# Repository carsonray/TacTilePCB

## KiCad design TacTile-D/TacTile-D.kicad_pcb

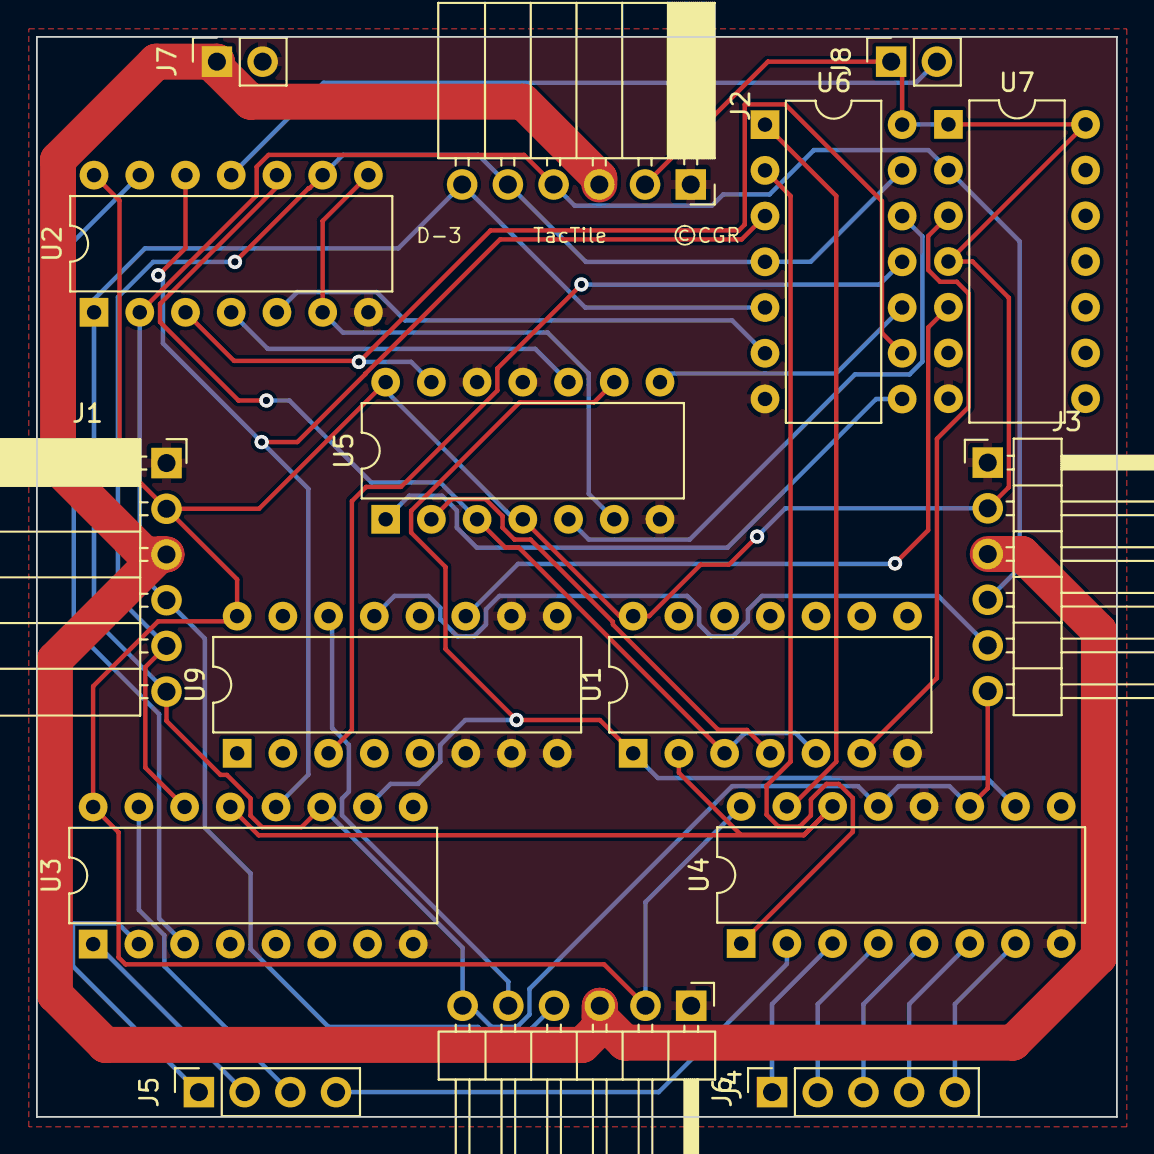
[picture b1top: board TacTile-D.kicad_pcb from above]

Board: 2 copper layers, 60.0 x 60.0 mm, 16 parts (0 on the bottom side), 36 nets.

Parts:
J1, J2: Conn_01x06; PinSocket_1x06_P2.54mm_Horizontal
J3, J4: Conn_01x06; PinHeader_1x06_P2.54mm_Horizontal
J5: Conn_01x04; PinSocket_1x04_P2.54mm_Vertical
J6: Conn_01x05; PinSocket_1x05_P2.54mm_Vertical
J7, J8: Conn_01x02; PinSocket_1x02_P2.54mm_Vertical
U1: 74LS04; DIP-14_W7.62mm
U2: 4011; DIP-14_W7.62mm
U3: 74HC595; DIP-16_W7.62mm
U4: 74HC590; DIP-16_W7.62mm
U5, U7: 74LS74; DIP-14_W7.62mm
U6: 74HC08; DIP-14_W7.62mm
U9: 74HC4051; DIP-16_W7.62mm

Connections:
CLK: J1.6, J2.6, J3.6, J4.6, U2.1, U3.11 (SRCLK), U4.11 (CPC), U4.13 (CPR), U6.5
GND: J1.1, J2.1, J3.1, J4.1, J7.2, U1.7 (GND), U2.7 (VSS), U3.8 (GND), U4.8 (GND), U4.12 (~CE), U5.7 (GND), U5.11 (C), U5.12 (D), U6.7 (GND), U7.7 (GND), U9.6 (~E), U9.7 (VEE), U9.8 (GND), U9.9 (S2), U9.10 (S1)
LEN: J8.2, U2.11
LS0: J5.1, U3.2 (QC)
LS1: J5.2, U3.1 (QB)
LS2: J5.3, U3.15 (QA)
LS3: J5.4, U4.2 (Q2)
LS4: J6.1, U4.3 (Q3)
LS5: J6.2, U4.4 (Q4)
LS6: J6.3, U4.5 (Q5)
LS7: J6.4, U4.6 (Q6)
LS8: J6.5, U4.7 (Q7)
MISO0: J3.5, U9.13 (A0)
MISO1: J4.5, U9.14 (A1)
MOSI: J1.5, J2.5, U2.9, U3.14 (SER), U6.4, U6.13
unnamed: U2.5, U6.6
unnamed: U2.13, U3.3 (QD)
unnamed: U2.12, U3.12 (RCLK), U6.3
unnamed: U1.2, U3.13 (~OE), U4.14 (~OE)
unnamed: U4.15 (Q0), U6.1
unnamed: U4.1 (Q1), U6.2
unnamed: U1.3, U1.5, U2.10, U5.3 (C)
unnamed: U1.4, U5.2 (D)
unnamed: U5.5 (Q), U6.12
unnamed: U2.6, U2.8, U5.6 (~Q)
unnamed: U5.1 (~R), U6.8
unnamed: U5.8 (~Q), U6.10
unnamed: U2.3, U5.13 (~R), U6.9
unnamed: U2.4, U5.10 (~S)
unnamed: U1.6, U7.3 (C)
unnamed: U7.5 (Q), U9.11 (S0)
unnamed: U6.11, U9.3 (A)
SEN: U1.1, U3.10 (~SRCLR), U4.10 (~MRC), U5.9 (Q)
SS: J1.4, J2.4, J3.4, J4.4, U2.2, U7.2 (D)
VCC: J1.2, J2.2, J3.2, J4.2, J8.1, U1.14 (VCC), U2.14 (VDD), U3.16 (VCC), U4.16 (VCC), U5.4 (~S), U5.14 (VCC), U6.14 (VCC), U7.1 (~R), U7.4 (~S), U7.14 (VCC), U9.16 (VCC)
VIN: J1.3, J2.3, J3.3, J4.3, J7.1

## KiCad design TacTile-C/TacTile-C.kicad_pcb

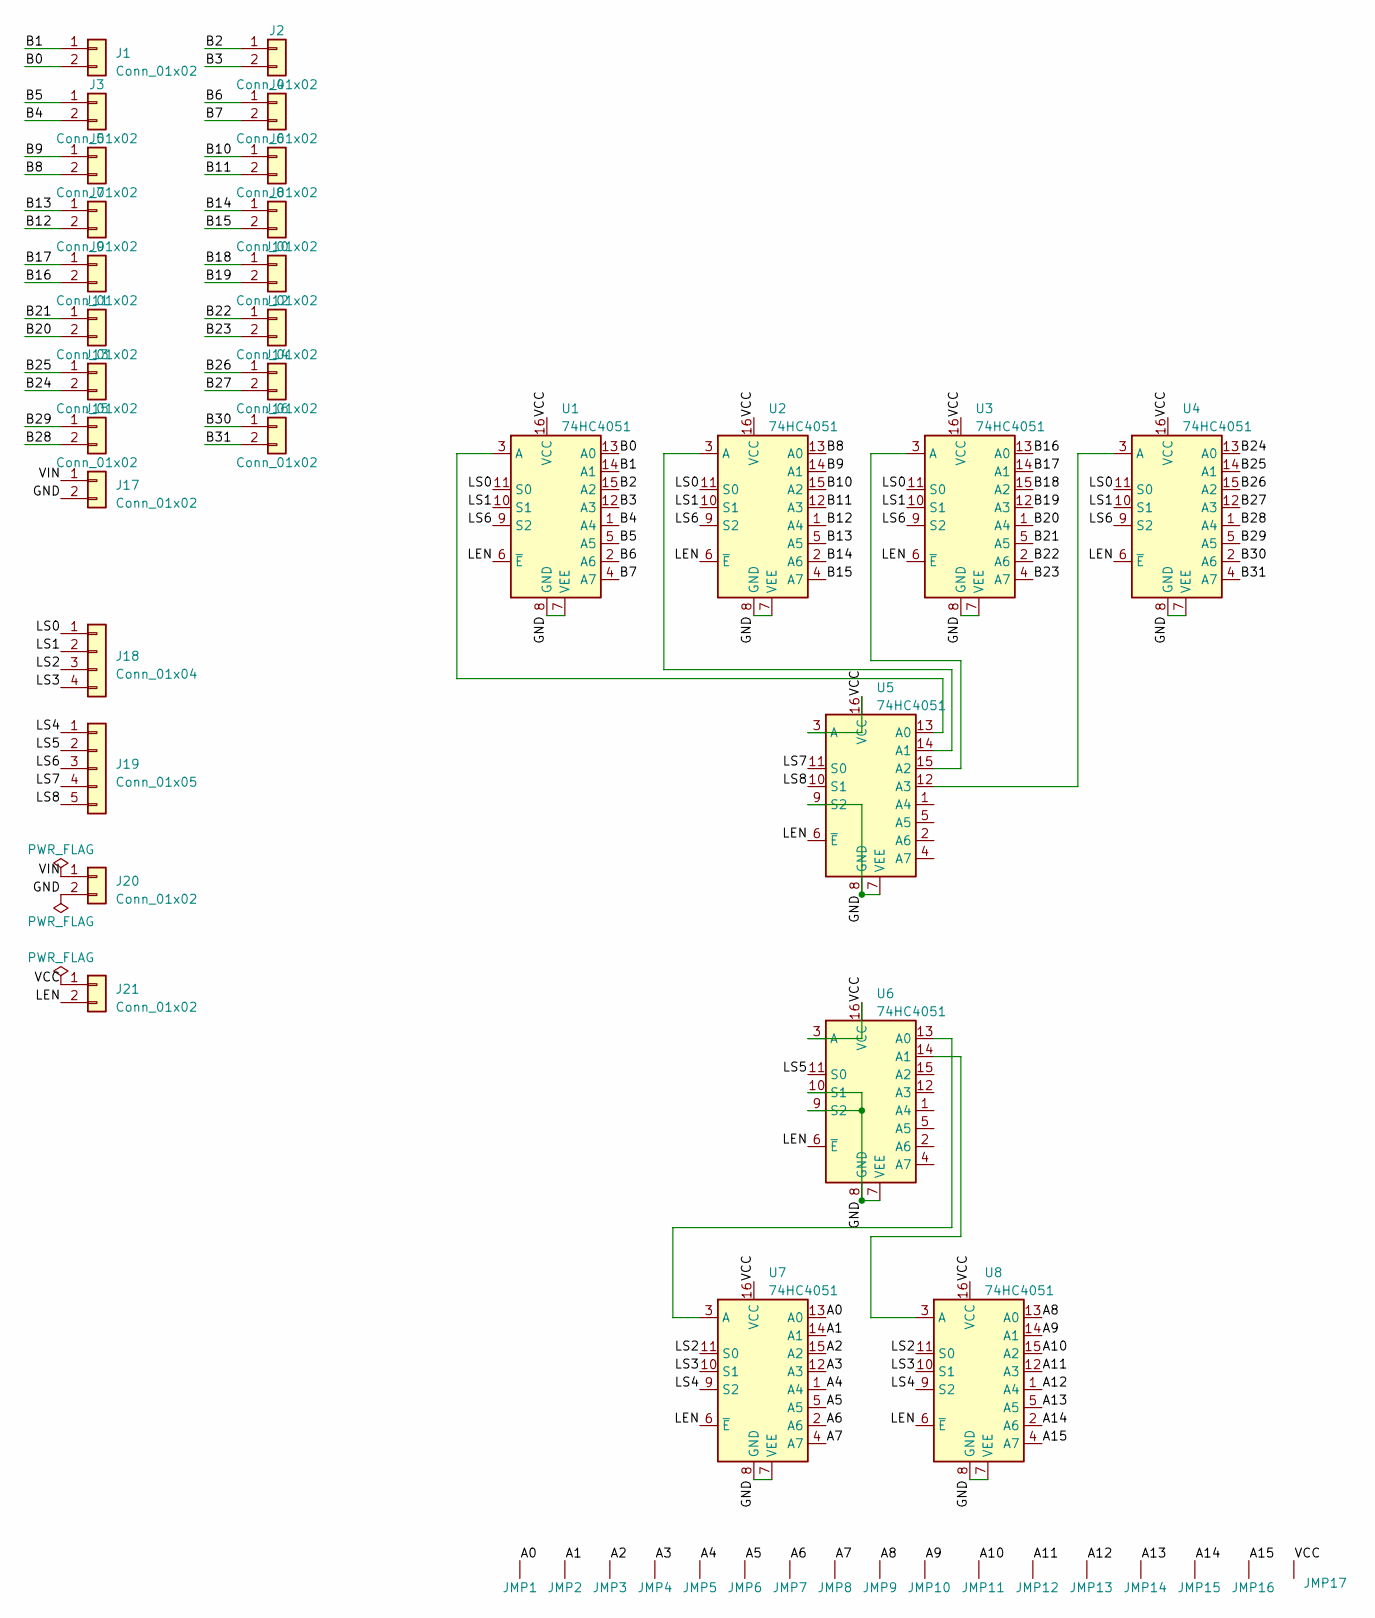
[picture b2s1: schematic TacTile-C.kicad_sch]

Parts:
J1, J2, J3, J4, J5, J6, J7, J8, J9, J10, J11, J12, J13, J14, J15, J16, J17: Conn_01x02; PinSocket_1x02_P1.27mm_Vertical
J18: Conn_01x04; PinHeader_1x04_P2.54mm_Vertical
J19: Conn_01x05; PinHeader_1x05_P2.54mm_Vertical
J20, J21: Conn_01x02; PinHeader_1x02_P2.54mm_Vertical
JMP1, JMP2, JMP3, JMP4, JMP5, JMP6, JMP7, JMP8, JMP9, JMP10, JMP11, JMP12, JMP13, JMP14, JMP15, JMP16, JMP17: Jumper_Connect
U1, U2, U3, U4, U5, U6, U7, U8: 74HC4051; DIP-16_W7.62mm

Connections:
/A0: JMP1.1 (A), U7.13 (A0)
/A1: JMP2.1 (A), U7.14 (A1)
/A2: JMP3.1 (A), U7.15 (A2)
/A3: JMP4.1 (A), U7.12 (A3)
/A4: JMP5.1 (A), U7.1 (A4)
/A5: JMP6.1 (A), U7.5 (A5)
/A6: JMP7.1 (A), U7.2 (A6)
/A7: JMP8.1 (A), U7.4 (A7)
/A8: JMP9.1 (A), U8.13 (A0)
/A9: JMP10.1 (A), U8.14 (A1)
/A10: JMP11.1 (A), U8.15 (A2)
/A11: JMP12.1 (A), U8.12 (A3)
/A12: JMP13.1 (A), U8.1 (A4)
/A13: JMP14.1 (A), U8.5 (A5)
/A14: JMP15.1 (A), U8.2 (A6)
/A15: JMP16.1 (A), U8.4 (A7)
/B0: J1.2, U1.13 (A0)
/B1: J1.1, U1.14 (A1)
/B2: J2.1, U1.15 (A2)
/B3: J2.2, U1.12 (A3)
/B4: J3.2, U1.1 (A4)
/B5: J3.1, U1.5 (A5)
/B6: J4.1, U1.2 (A6)
/B7: J4.2, U1.4 (A7)
/B8: J5.2, U2.13 (A0)
/B9: J5.1, U2.14 (A1)
/B10: J6.1, U2.15 (A2)
/B11: J6.2, U2.12 (A3)
/B12: J7.2, U2.1 (A4)
/B13: J7.1, U2.5 (A5)
/B14: J8.1, U2.2 (A6)
/B15: J8.2, U2.4 (A7)
/B16: J9.2, U3.13 (A0)
/B17: J9.1, U3.14 (A1)
/B18: J10.1, U3.15 (A2)
/B19: J10.2, U3.12 (A3)
/B20: J11.2, U3.1 (A4)
/B21: J11.1, U3.5 (A5)
/B22: J12.1, U3.2 (A6)
/B23: J12.2, U3.4 (A7)
/B24: J13.2, U4.13 (A0)
/B25: J13.1, U4.14 (A1)
/B26: J14.1, U4.15 (A2)
/B27: J14.2, U4.12 (A3)
/B28: J15.2, U4.1 (A4)
/B29: J15.1, U4.5 (A5)
/B30: J16.1, U4.2 (A6)
/B31: J16.2, U4.4 (A7)
/GND: J17.2, J20.2, U1.7 (VEE), U1.8 (GND), U2.7 (VEE), U2.8 (GND), U3.7 (VEE), U3.8 (GND), U4.7 (VEE), U4.8 (GND), U5.7 (VEE), U5.8 (GND), U5.9 (S2), U6.7 (VEE), U6.8 (GND), U6.9 (S2), U6.10 (S1), U7.7 (VEE), U7.8 (GND), U8.7 (VEE), U8.8 (GND)
/LEN: J21.2, U1.6 (~E), U2.6 (~E), U3.6 (~E), U4.6 (~E), U5.6 (~E), U6.6 (~E), U7.6 (~E), U8.6 (~E)
/LS0: J18.1, U1.11 (S0), U2.11 (S0), U3.11 (S0), U4.11 (S0)
/LS1: J18.2, U1.10 (S1), U2.10 (S1), U3.10 (S1), U4.10 (S1)
/LS2: J18.3, U7.11 (S0), U8.11 (S0)
/LS3: J18.4, U7.10 (S1), U8.10 (S1)
/LS4: J19.1, U7.9 (S2), U8.9 (S2)
/LS5: J19.2, U6.11 (S0)
/LS6: J19.3, U1.9 (S2), U2.9 (S2), U3.9 (S2), U4.9 (S2)
/LS7: J19.4, U5.11 (S0)
/LS8: J19.5, U5.10 (S1)
/VCC: J21.1, JMP17.1 (A), U1.16 (VCC), U2.16 (VCC), U3.16 (VCC), U4.16 (VCC), U5.3 (A), U5.16 (VCC), U6.3 (A), U6.16 (VCC), U7.16 (VCC), U8.16 (VCC)
/VIN: J17.1, J20.1
unnamed: U1.3 (A), U5.13 (A0)
unnamed: U2.3 (A), U5.14 (A1)
unnamed: U3.3 (A), U5.15 (A2)
unnamed: U4.3 (A), U5.12 (A3)
unnamed: U6.13 (A0), U7.3 (A)
unnamed: U6.14 (A1), U8.3 (A)

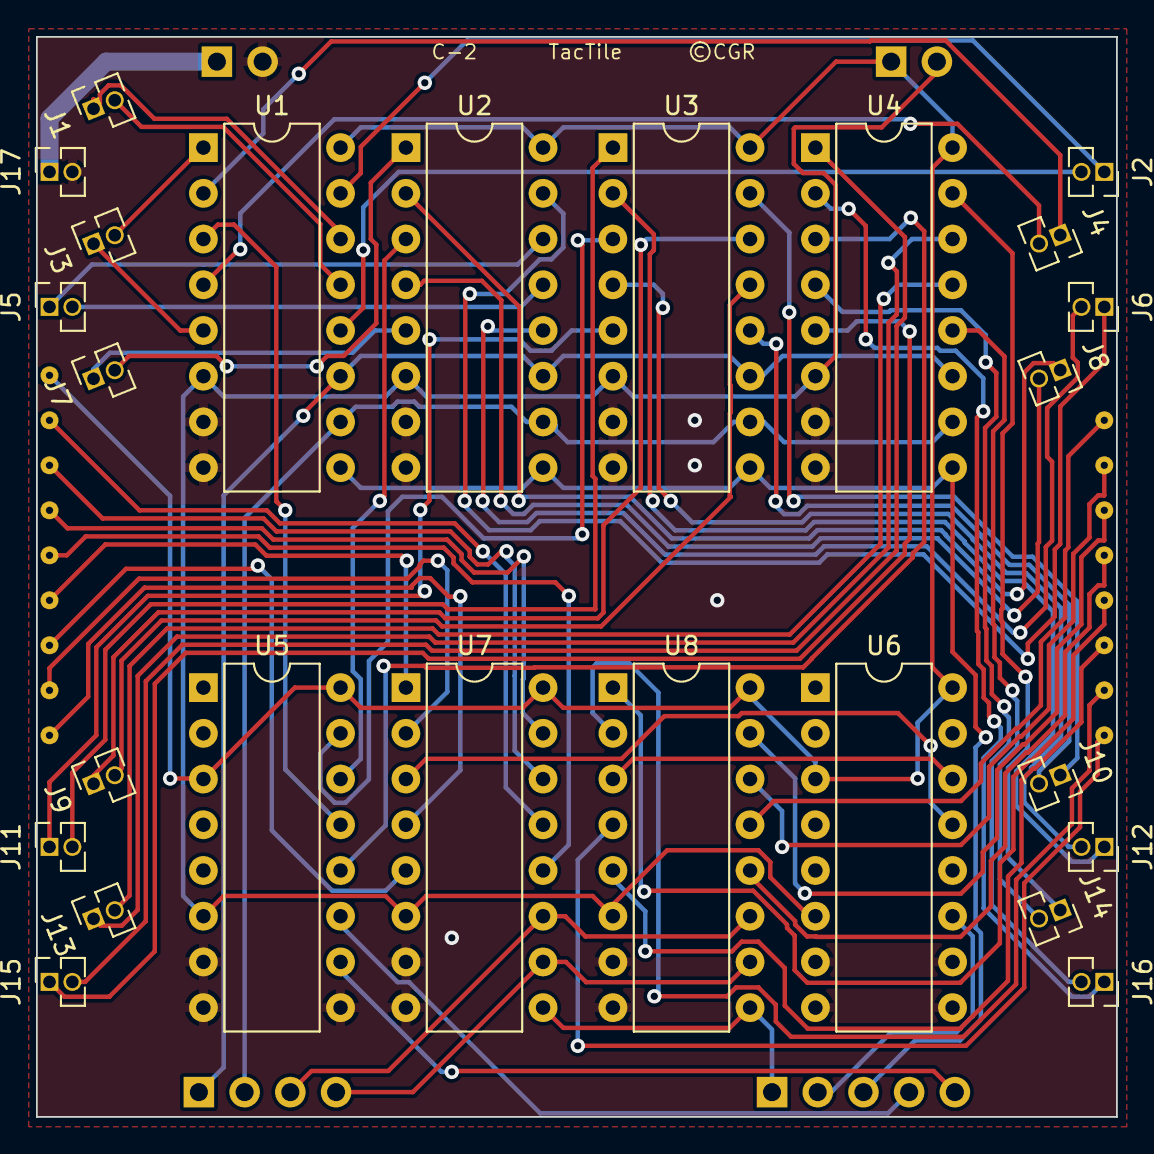
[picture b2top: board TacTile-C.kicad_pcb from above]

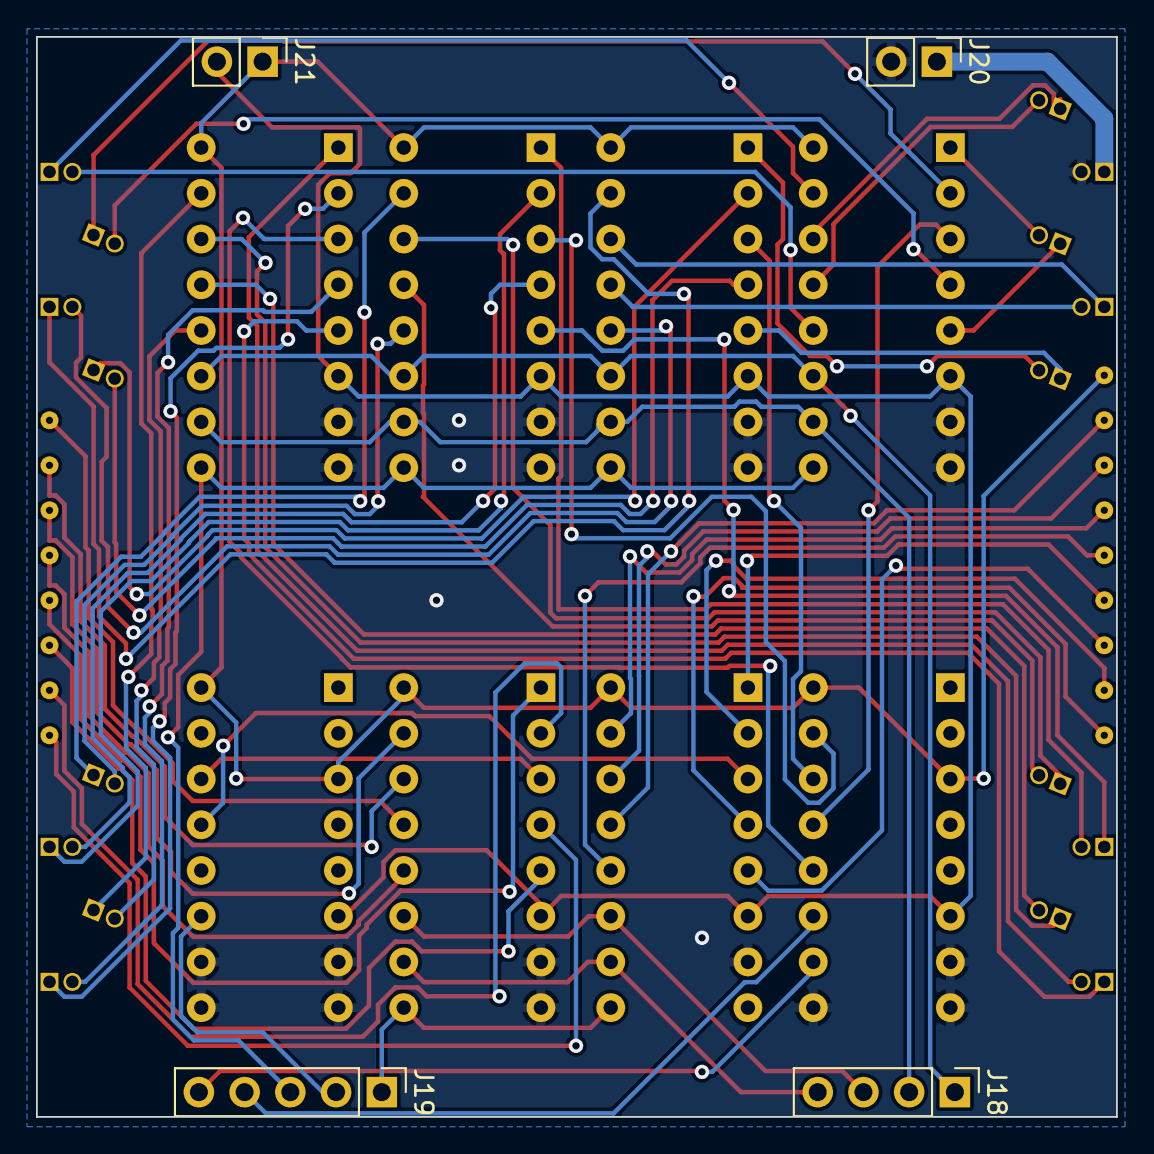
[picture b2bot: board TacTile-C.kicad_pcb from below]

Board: 2 copper layers, 60.0 x 60.0 mm, 46 parts (4 on the bottom side), 67 nets.

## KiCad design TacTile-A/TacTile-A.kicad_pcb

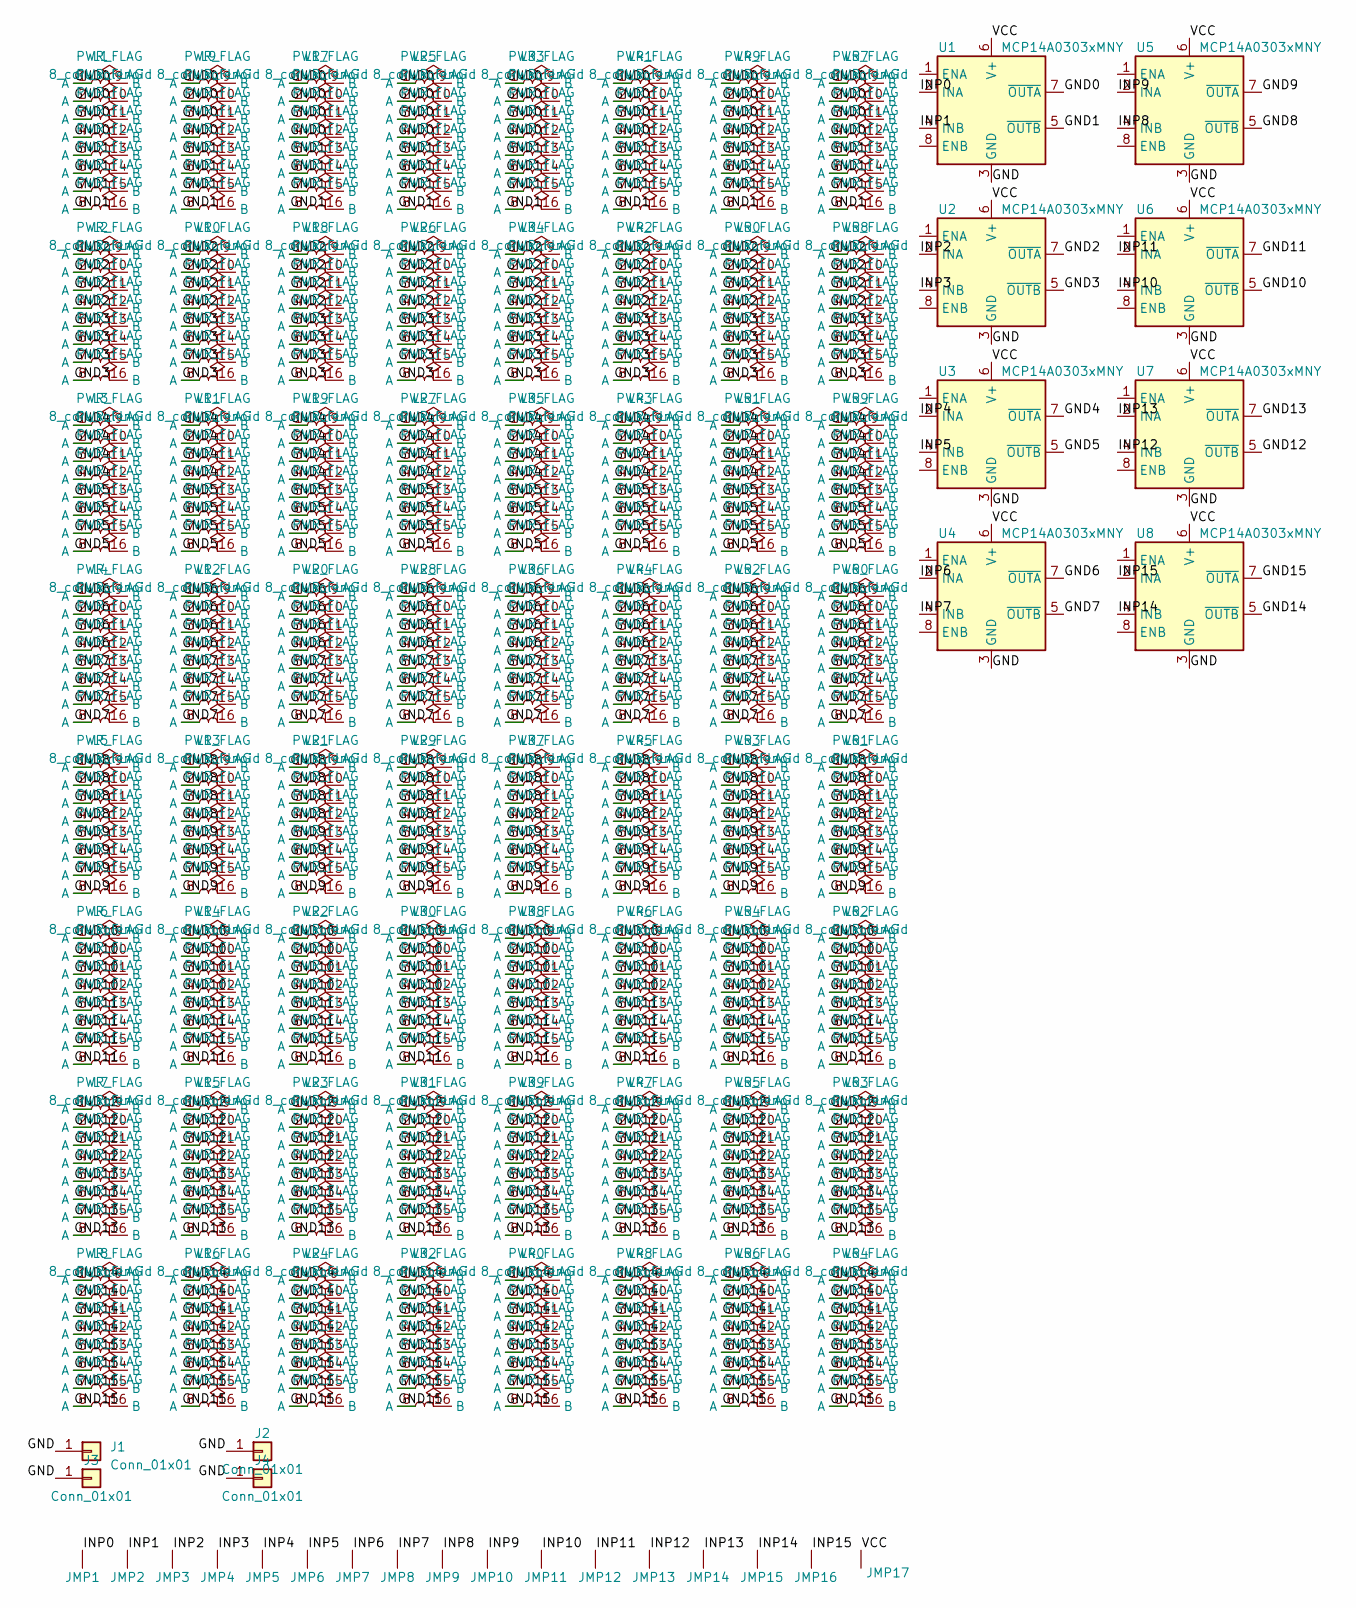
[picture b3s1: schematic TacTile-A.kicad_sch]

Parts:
J1, J3: Conn_01x01; PinSocket_1x01_P2.54mm_Horizontal
J2, J4: Conn_01x01; PinHeader_1x01_P2.54mm_Horizontal
JMP1, JMP2, JMP3, JMP4, JMP5, JMP6, JMP7, JMP8, JMP9, JMP10, JMP11, JMP12, JMP13, JMP14, JMP15, JMP16, JMP17: Jumper_Connect
L1, L2, L3, L4, L5, L6, L7, L8, L9, L10, L11, L12, L13, L14, L15, L16, L17, L18, L19, L20, L21, L22, L23, L24, L25, L26, L27, L28, L29, L30, L31, L32, L33, L34, L35, L36, L37, L38, L39, L40, L41, L42, L43, L44, L45, L46, L47, L48, L49, L50, L51, L52, L53, L54, L55, L56, L57, L58, L59, L60, L61, L62, L63, L64: 8_coil_solenoid
U1, U2, U3, U4, U5, U6, U7, U8: MCP14A0303xMNY; WDFN-8-1EP_3x2mm_P0.5mm_EP1.3x1.4mm

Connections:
/GND: J1.1, J2.1, J3.1, J4.1, U1.3 (GND), U1.9 (GND), U2.3 (GND), U2.9 (GND), U3.3 (GND), U3.9 (GND), U4.3 (GND), U4.9 (GND), U5.3 (GND), U5.9 (GND), U6.3 (GND), U6.9 (GND), U7.3 (GND), U7.9 (GND), U8.3 (GND), U8.9 (GND)
/GND0: L1.1 (A), L1.2 (A), L1.3 (A), L1.4 (A), L9.1 (A), L9.2 (A), L9.3 (A), L9.4 (A), L17.1 (A), L17.2 (A), L17.3 (A), L17.4 (A), L25.1 (A), L25.2 (A), L25.3 (A), L25.4 (A), L33.1 (A), L33.2 (A), L33.3 (A), L33.4 (A), L41.1 (A), L41.2 (A), L41.3 (A), L41.4 (A), L49.1 (A), L49.2 (A), L49.3 (A), L49.4 (A), L57.1 (A), L57.2 (A), L57.3 (A), L57.4 (A), U1.7 (~OUTA)
/GND1: L1.5 (A), L1.6 (A), L1.7 (A), L1.8 (A), L9.5 (A), L9.6 (A), L9.7 (A), L9.8 (A), L17.5 (A), L17.6 (A), L17.7 (A), L17.8 (A), L25.5 (A), L25.6 (A), L25.7 (A), L25.8 (A), L33.5 (A), L33.6 (A), L33.7 (A), L33.8 (A), L41.5 (A), L41.6 (A), L41.7 (A), L41.8 (A), L49.5 (A), L49.6 (A), L49.7 (A), L49.8 (A), L57.5 (A), L57.6 (A), L57.7 (A), L57.8 (A), U1.5 (~OUTB)
/GND2: L2.1 (A), L2.2 (A), L2.3 (A), L2.4 (A), L10.1 (A), L10.2 (A), L10.3 (A), L10.4 (A), L18.1 (A), L18.2 (A), L18.3 (A), L18.4 (A), L26.1 (A), L26.2 (A), L26.3 (A), L26.4 (A), L34.1 (A), L34.2 (A), L34.3 (A), L34.4 (A), L42.1 (A), L42.2 (A), L42.3 (A), L42.4 (A), L50.1 (A), L50.2 (A), L50.3 (A), L50.4 (A), L58.1 (A), L58.2 (A), L58.3 (A), L58.4 (A), U2.7 (~OUTA)
/GND3: L2.5 (A), L2.6 (A), L2.7 (A), L2.8 (A), L10.5 (A), L10.6 (A), L10.7 (A), L10.8 (A), L18.5 (A), L18.6 (A), L18.7 (A), L18.8 (A), L26.5 (A), L26.6 (A), L26.7 (A), L26.8 (A), L34.5 (A), L34.6 (A), L34.7 (A), L34.8 (A), L42.5 (A), L42.6 (A), L42.7 (A), L42.8 (A), L50.5 (A), L50.6 (A), L50.7 (A), L50.8 (A), L58.5 (A), L58.6 (A), L58.7 (A), L58.8 (A), U2.5 (~OUTB)
/GND4: L3.1 (A), L3.2 (A), L3.3 (A), L3.4 (A), L11.1 (A), L11.2 (A), L11.3 (A), L11.4 (A), L19.1 (A), L19.2 (A), L19.3 (A), L19.4 (A), L27.1 (A), L27.2 (A), L27.3 (A), L27.4 (A), L35.1 (A), L35.2 (A), L35.3 (A), L35.4 (A), L43.1 (A), L43.2 (A), L43.3 (A), L43.4 (A), L51.1 (A), L51.2 (A), L51.3 (A), L51.4 (A), L59.1 (A), L59.2 (A), L59.3 (A), L59.4 (A), U3.7 (~OUTA)
/GND5: L3.5 (A), L3.6 (A), L3.7 (A), L3.8 (A), L11.5 (A), L11.6 (A), L11.7 (A), L11.8 (A), L19.5 (A), L19.6 (A), L19.7 (A), L19.8 (A), L27.5 (A), L27.6 (A), L27.7 (A), L27.8 (A), L35.5 (A), L35.6 (A), L35.7 (A), L35.8 (A), L43.5 (A), L43.6 (A), L43.7 (A), L43.8 (A), L51.5 (A), L51.6 (A), L51.7 (A), L51.8 (A), L59.5 (A), L59.6 (A), L59.7 (A), L59.8 (A), U3.5 (~OUTB)
/GND6: L4.1 (A), L4.2 (A), L4.3 (A), L4.4 (A), L12.1 (A), L12.2 (A), L12.3 (A), L12.4 (A), L20.1 (A), L20.2 (A), L20.3 (A), L20.4 (A), L28.1 (A), L28.2 (A), L28.3 (A), L28.4 (A), L36.1 (A), L36.2 (A), L36.3 (A), L36.4 (A), L44.1 (A), L44.2 (A), L44.3 (A), L44.4 (A), L52.1 (A), L52.2 (A), L52.3 (A), L52.4 (A), L60.1 (A), L60.2 (A), L60.3 (A), L60.4 (A), U4.7 (~OUTA)
/GND7: L4.5 (A), L4.6 (A), L4.7 (A), L4.8 (A), L12.5 (A), L12.6 (A), L12.7 (A), L12.8 (A), L20.5 (A), L20.6 (A), L20.7 (A), L20.8 (A), L28.5 (A), L28.6 (A), L28.7 (A), L28.8 (A), L36.5 (A), L36.6 (A), L36.7 (A), L36.8 (A), L44.5 (A), L44.6 (A), L44.7 (A), L44.8 (A), L52.5 (A), L52.6 (A), L52.7 (A), L52.8 (A), L60.5 (A), L60.6 (A), L60.7 (A), L60.8 (A), U4.5 (~OUTB)
/GND8: L5.1 (A), L5.2 (A), L5.3 (A), L5.4 (A), L13.1 (A), L13.2 (A), L13.3 (A), L13.4 (A), L21.1 (A), L21.2 (A), L21.3 (A), L21.4 (A), L29.1 (A), L29.2 (A), L29.3 (A), L29.4 (A), L37.1 (A), L37.2 (A), L37.3 (A), L37.4 (A), L45.1 (A), L45.2 (A), L45.3 (A), L45.4 (A), L53.1 (A), L53.2 (A), L53.3 (A), L53.4 (A), L61.1 (A), L61.2 (A), L61.3 (A), L61.4 (A), U5.5 (~OUTB)
/GND9: L5.5 (A), L5.6 (A), L5.7 (A), L5.8 (A), L13.5 (A), L13.6 (A), L13.7 (A), L13.8 (A), L21.5 (A), L21.6 (A), L21.7 (A), L21.8 (A), L29.5 (A), L29.6 (A), L29.7 (A), L29.8 (A), L37.5 (A), L37.6 (A), L37.7 (A), L37.8 (A), L45.5 (A), L45.6 (A), L45.7 (A), L45.8 (A), L53.5 (A), L53.6 (A), L53.7 (A), L53.8 (A), L61.5 (A), L61.6 (A), L61.7 (A), L61.8 (A), U5.7 (~OUTA)
/GND10: L6.1 (A), L6.2 (A), L6.3 (A), L6.4 (A), L14.1 (A), L14.2 (A), L14.3 (A), L14.4 (A), L22.1 (A), L22.2 (A), L22.3 (A), L22.4 (A), L30.1 (A), L30.2 (A), L30.3 (A), L30.4 (A), L38.1 (A), L38.2 (A), L38.3 (A), L38.4 (A), L46.1 (A), L46.2 (A), L46.3 (A), L46.4 (A), L54.1 (A), L54.2 (A), L54.3 (A), L54.4 (A), L62.1 (A), L62.2 (A), L62.3 (A), L62.4 (A), U6.5 (~OUTB)
/GND11: L6.5 (A), L6.6 (A), L6.7 (A), L6.8 (A), L14.5 (A), L14.6 (A), L14.7 (A), L14.8 (A), L22.5 (A), L22.6 (A), L22.7 (A), L22.8 (A), L30.5 (A), L30.6 (A), L30.7 (A), L30.8 (A), L38.5 (A), L38.6 (A), L38.7 (A), L38.8 (A), L46.5 (A), L46.6 (A), L46.7 (A), L46.8 (A), L54.5 (A), L54.6 (A), L54.7 (A), L54.8 (A), L62.5 (A), L62.6 (A), L62.7 (A), L62.8 (A), U6.7 (~OUTA)
/GND12: L7.1 (A), L7.2 (A), L7.3 (A), L7.4 (A), L15.1 (A), L15.2 (A), L15.3 (A), L15.4 (A), L23.1 (A), L23.2 (A), L23.3 (A), L23.4 (A), L31.1 (A), L31.2 (A), L31.3 (A), L31.4 (A), L39.1 (A), L39.2 (A), L39.3 (A), L39.4 (A), L47.1 (A), L47.2 (A), L47.3 (A), L47.4 (A), L55.1 (A), L55.2 (A), L55.3 (A), L55.4 (A), L63.1 (A), L63.2 (A), L63.3 (A), L63.4 (A), U7.5 (~OUTB)
/GND13: L7.5 (A), L7.6 (A), L7.7 (A), L7.8 (A), L15.5 (A), L15.6 (A), L15.7 (A), L15.8 (A), L23.5 (A), L23.6 (A), L23.7 (A), L23.8 (A), L31.5 (A), L31.6 (A), L31.7 (A), L31.8 (A), L39.5 (A), L39.6 (A), L39.7 (A), L39.8 (A), L47.5 (A), L47.6 (A), L47.7 (A), L47.8 (A), L55.5 (A), L55.6 (A), L55.7 (A), L55.8 (A), L63.5 (A), L63.6 (A), L63.7 (A), L63.8 (A), U7.7 (~OUTA)
/GND14: L8.1 (A), L8.2 (A), L8.3 (A), L8.4 (A), L16.1 (A), L16.2 (A), L16.3 (A), L16.4 (A), L24.1 (A), L24.2 (A), L24.3 (A), L24.4 (A), L32.1 (A), L32.2 (A), L32.3 (A), L32.4 (A), L40.1 (A), L40.2 (A), L40.3 (A), L40.4 (A), L48.1 (A), L48.2 (A), L48.3 (A), L48.4 (A), L56.1 (A), L56.2 (A), L56.3 (A), L56.4 (A), L64.1 (A), L64.2 (A), L64.3 (A), L64.4 (A), U8.5 (~OUTB)
/GND15: L8.5 (A), L8.6 (A), L8.7 (A), L8.8 (A), L16.5 (A), L16.6 (A), L16.7 (A), L16.8 (A), L24.5 (A), L24.6 (A), L24.7 (A), L24.8 (A), L32.5 (A), L32.6 (A), L32.7 (A), L32.8 (A), L40.5 (A), L40.6 (A), L40.7 (A), L40.8 (A), L48.5 (A), L48.6 (A), L48.7 (A), L48.8 (A), L56.5 (A), L56.6 (A), L56.7 (A), L56.8 (A), L64.5 (A), L64.6 (A), L64.7 (A), L64.8 (A), U8.7 (~OUTA)
/INP0: JMP1.1 (A), U1.2 (INA)
/INP1: JMP2.1 (A), U1.4 (INB)
/INP2: JMP3.1 (A), U2.2 (INA)
/INP3: JMP4.1 (A), U2.4 (INB)
/INP4: JMP5.1 (A), U3.2 (INA)
/INP5: JMP6.1 (A), U3.4 (INB)
/INP6: JMP7.1 (A), U4.2 (INA)
/INP7: JMP8.1 (A), U4.4 (INB)
/INP8: JMP9.1 (A), U5.4 (INB)
/INP9: JMP10.1 (A), U5.2 (INA)
/INP10: JMP11.1 (A), U6.4 (INB)
/INP11: JMP12.1 (A), U6.2 (INA)
/INP12: JMP13.1 (A), U7.4 (INB)
/INP13: JMP14.1 (A), U7.2 (INA)
/INP14: JMP15.1 (A), U8.4 (INB)
/INP15: JMP16.1 (A), U8.2 (INA)
/VCC: JMP17.1 (A), U1.6 (V+), U2.6 (V+), U3.6 (V+), U4.6 (V+), U5.6 (V+), U6.6 (V+), U7.6 (V+), U8.6 (V+)

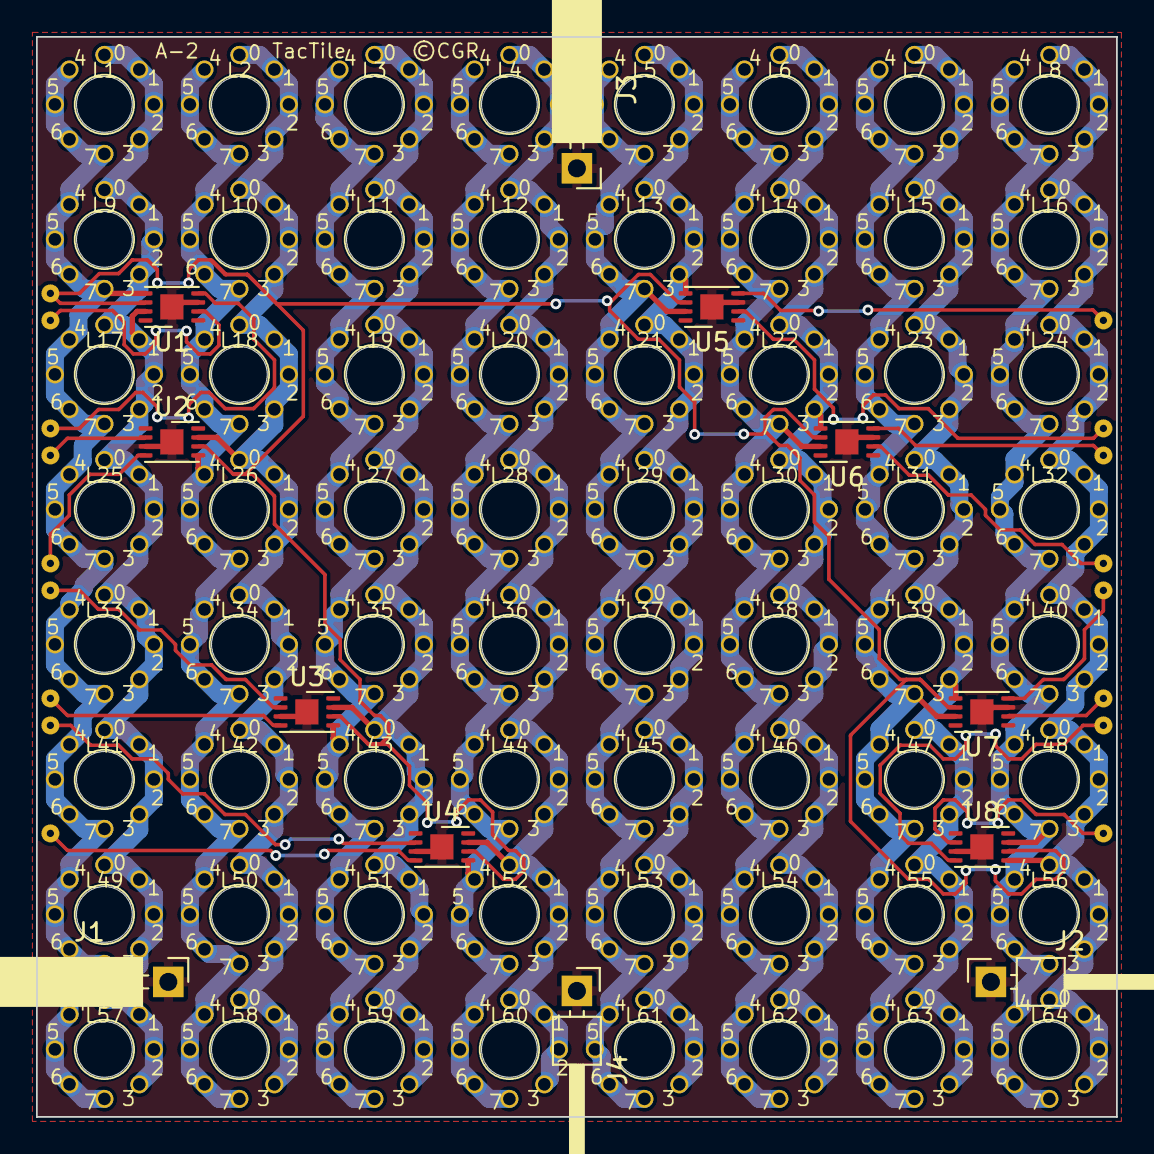
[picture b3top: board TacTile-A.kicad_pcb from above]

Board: 2 copper layers, 60.0 x 60.0 mm, 93 parts (0 on the bottom side), 34 nets.

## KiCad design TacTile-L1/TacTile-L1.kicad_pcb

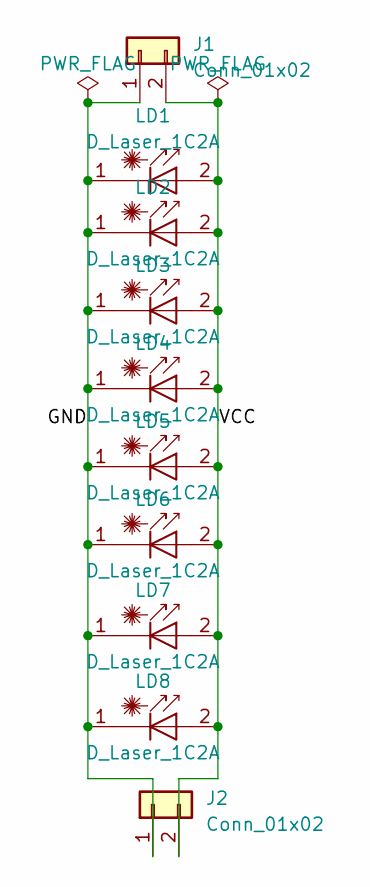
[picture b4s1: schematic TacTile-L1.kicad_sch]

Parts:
J1: Conn_01x02; PinSocket_1x02_P2.54mm_Horizontal
J2: Conn_01x02; PinHeader_1x02_P2.54mm_Horizontal
LD1, LD2, LD3, LD4, LD5, LD6, LD7, LD8: D_Laser_1C2A; Laser_Diode

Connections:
/GND: J1.1, J2.1, LD1.1 (K), LD2.1 (K), LD3.1 (K), LD4.1 (K), LD5.1 (K), LD6.1 (K), LD7.1 (K), LD8.1 (K)
/VCC: J1.2, J2.2, LD1.2 (A), LD2.2 (A), LD3.2 (A), LD4.2 (A), LD5.2 (A), LD6.2 (A), LD7.2 (A), LD8.2 (A)

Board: 2 copper layers, 10 parts (0 on the bottom side), 2 nets, no tracks yet.

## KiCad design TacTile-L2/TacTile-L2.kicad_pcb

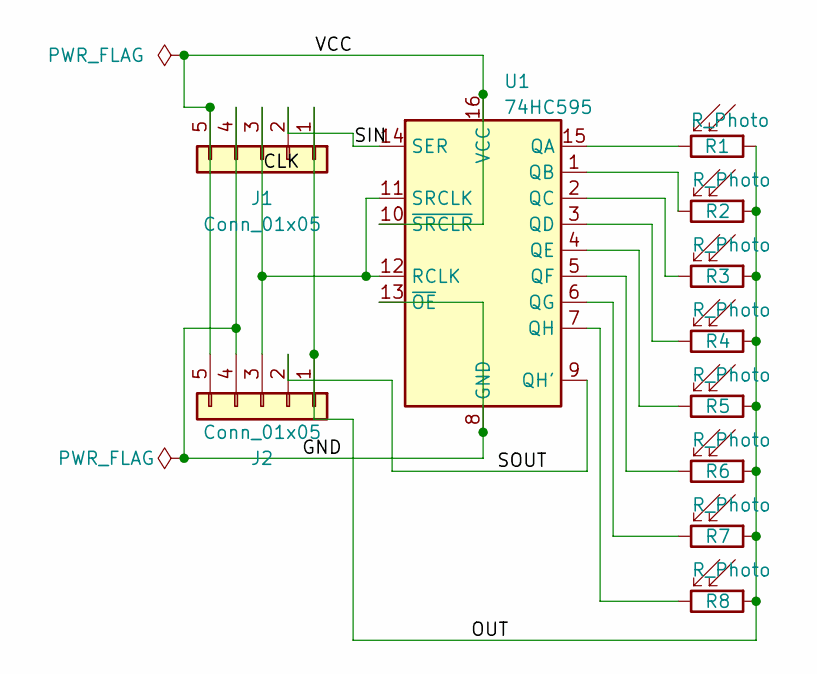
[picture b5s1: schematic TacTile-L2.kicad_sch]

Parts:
J1: Conn_01x05; PinSocket_1x05_P2.54mm_Horizontal
J2: Conn_01x05; PinHeader_1x05_P2.54mm_Horizontal
R1, R2, R3, R4, R5, R6, R7, R8: R_Photo; Photoresistor
U1: 74HC595; DIP-16_W7.62mm

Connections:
/CLK: J1.3, J2.3, U1.11 (SRCLK), U1.12 (RCLK)
/GND: J1.4, J2.4, U1.8 (GND), U1.13 (~OE)
/OUT: J1.1, J2.1, R1.1, R2.1, R3.1, R4.1, R5.1, R6.1, R7.1, R8.1
/SIN: J1.2, U1.14 (SER)
/SOUT: J2.2, U1.9 (QH')
/VCC: J1.5, J2.5, U1.10 (~SRCLR), U1.16 (VCC)
unnamed: R1.2, U1.15 (QA)
unnamed: R2.2, U1.1 (QB)
unnamed: R3.2, U1.2 (QC)
unnamed: R4.2, U1.3 (QD)
unnamed: R5.2, U1.4 (QE)
unnamed: R6.2, U1.5 (QF)
unnamed: R7.2, U1.6 (QG)
unnamed: R8.2, U1.7 (QH)

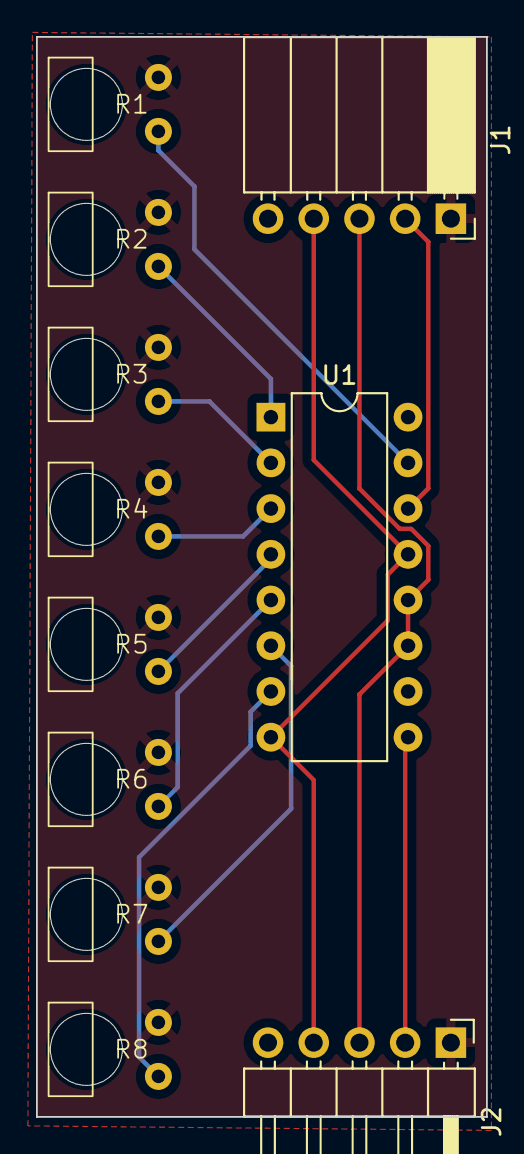
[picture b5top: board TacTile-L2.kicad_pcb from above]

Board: 2 copper layers, 25.0 x 60.0 mm, 11 parts (0 on the bottom side), 14 nets.

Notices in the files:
TacTile-A/TacTile-A.kicad_pcb:
©CGR
